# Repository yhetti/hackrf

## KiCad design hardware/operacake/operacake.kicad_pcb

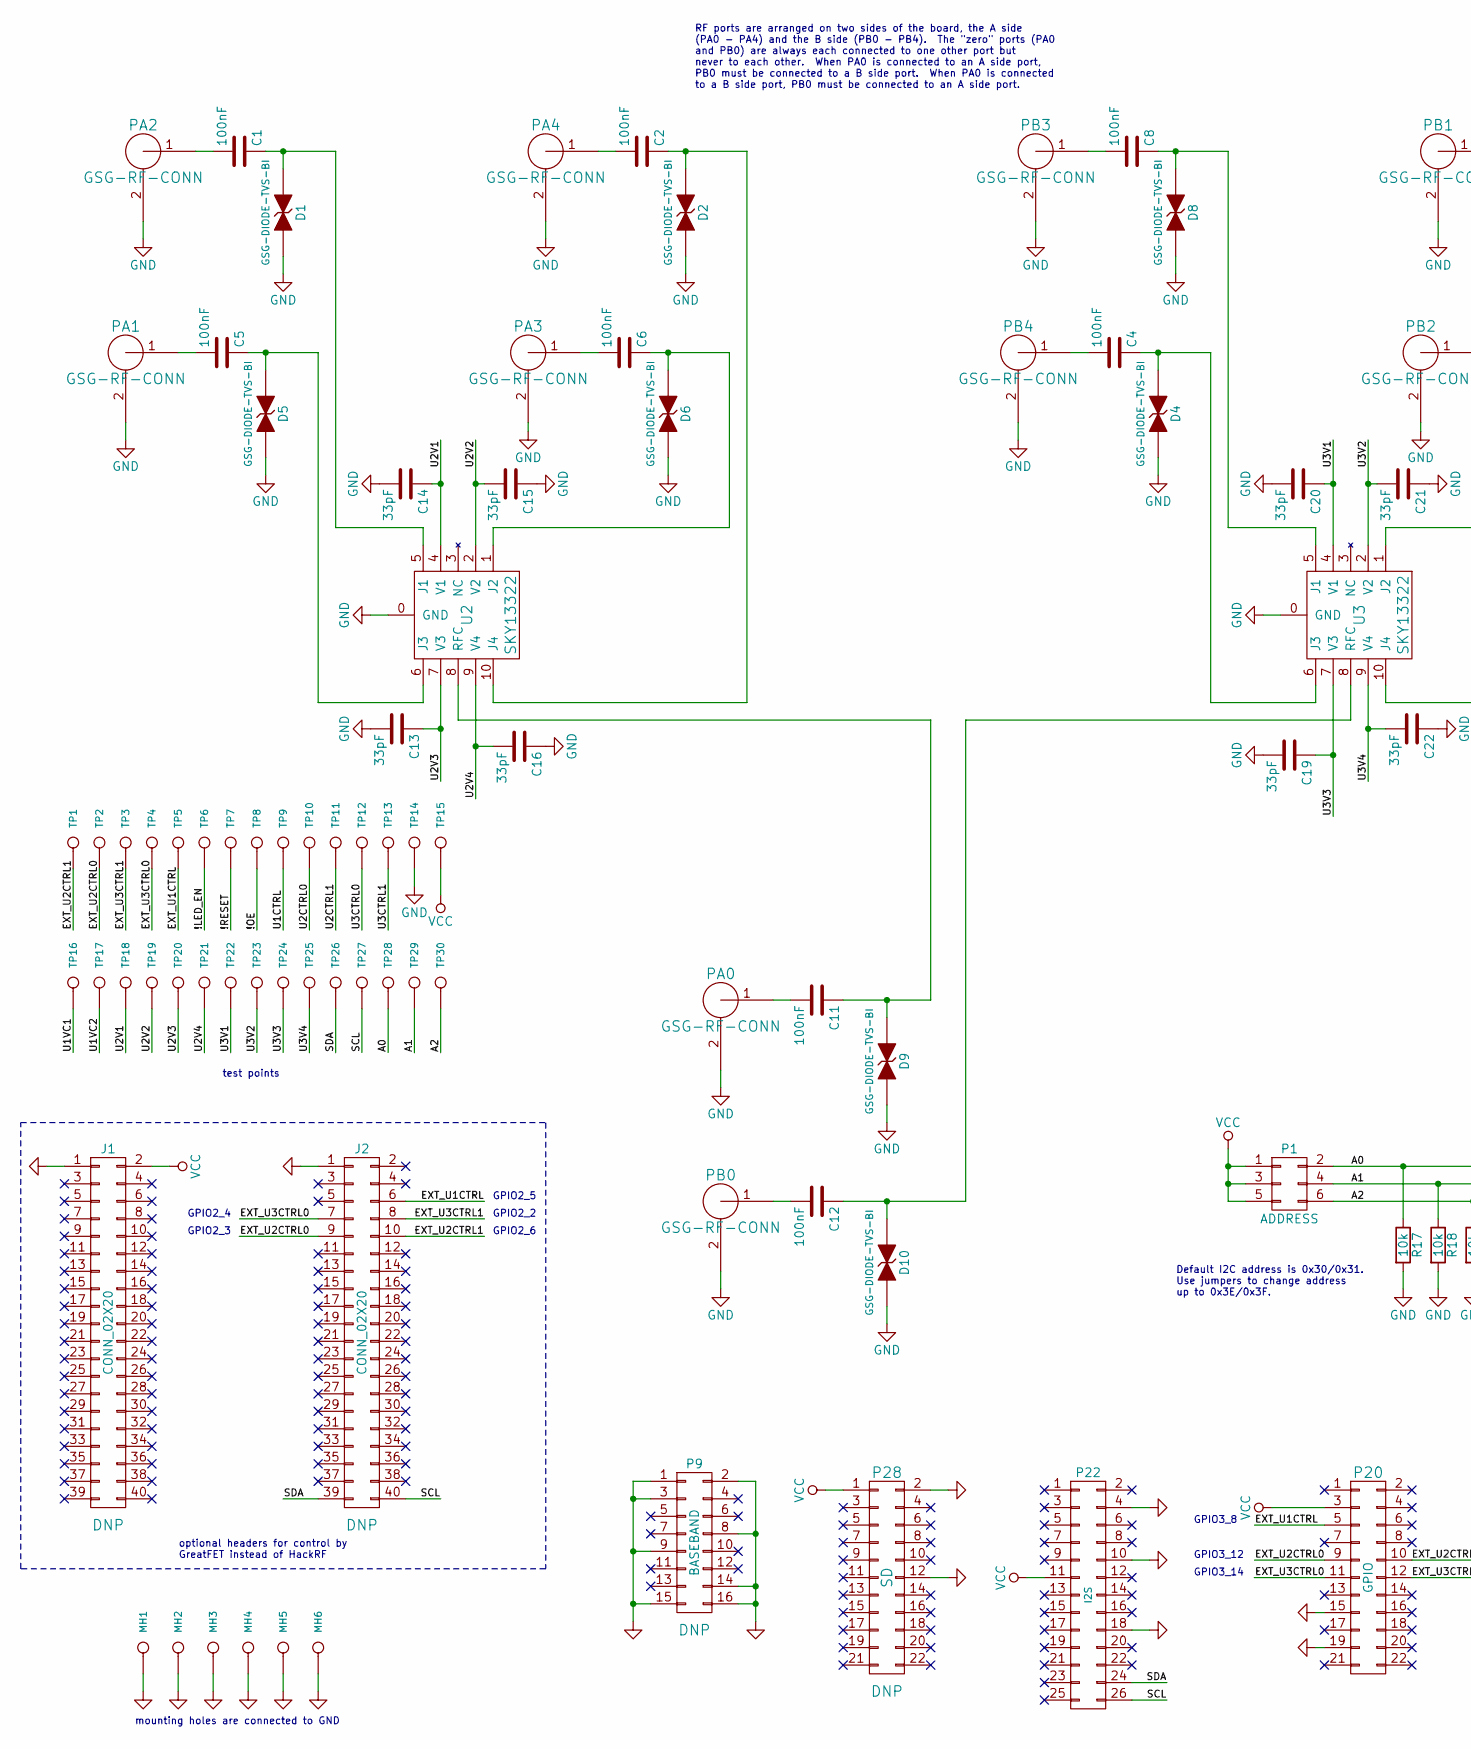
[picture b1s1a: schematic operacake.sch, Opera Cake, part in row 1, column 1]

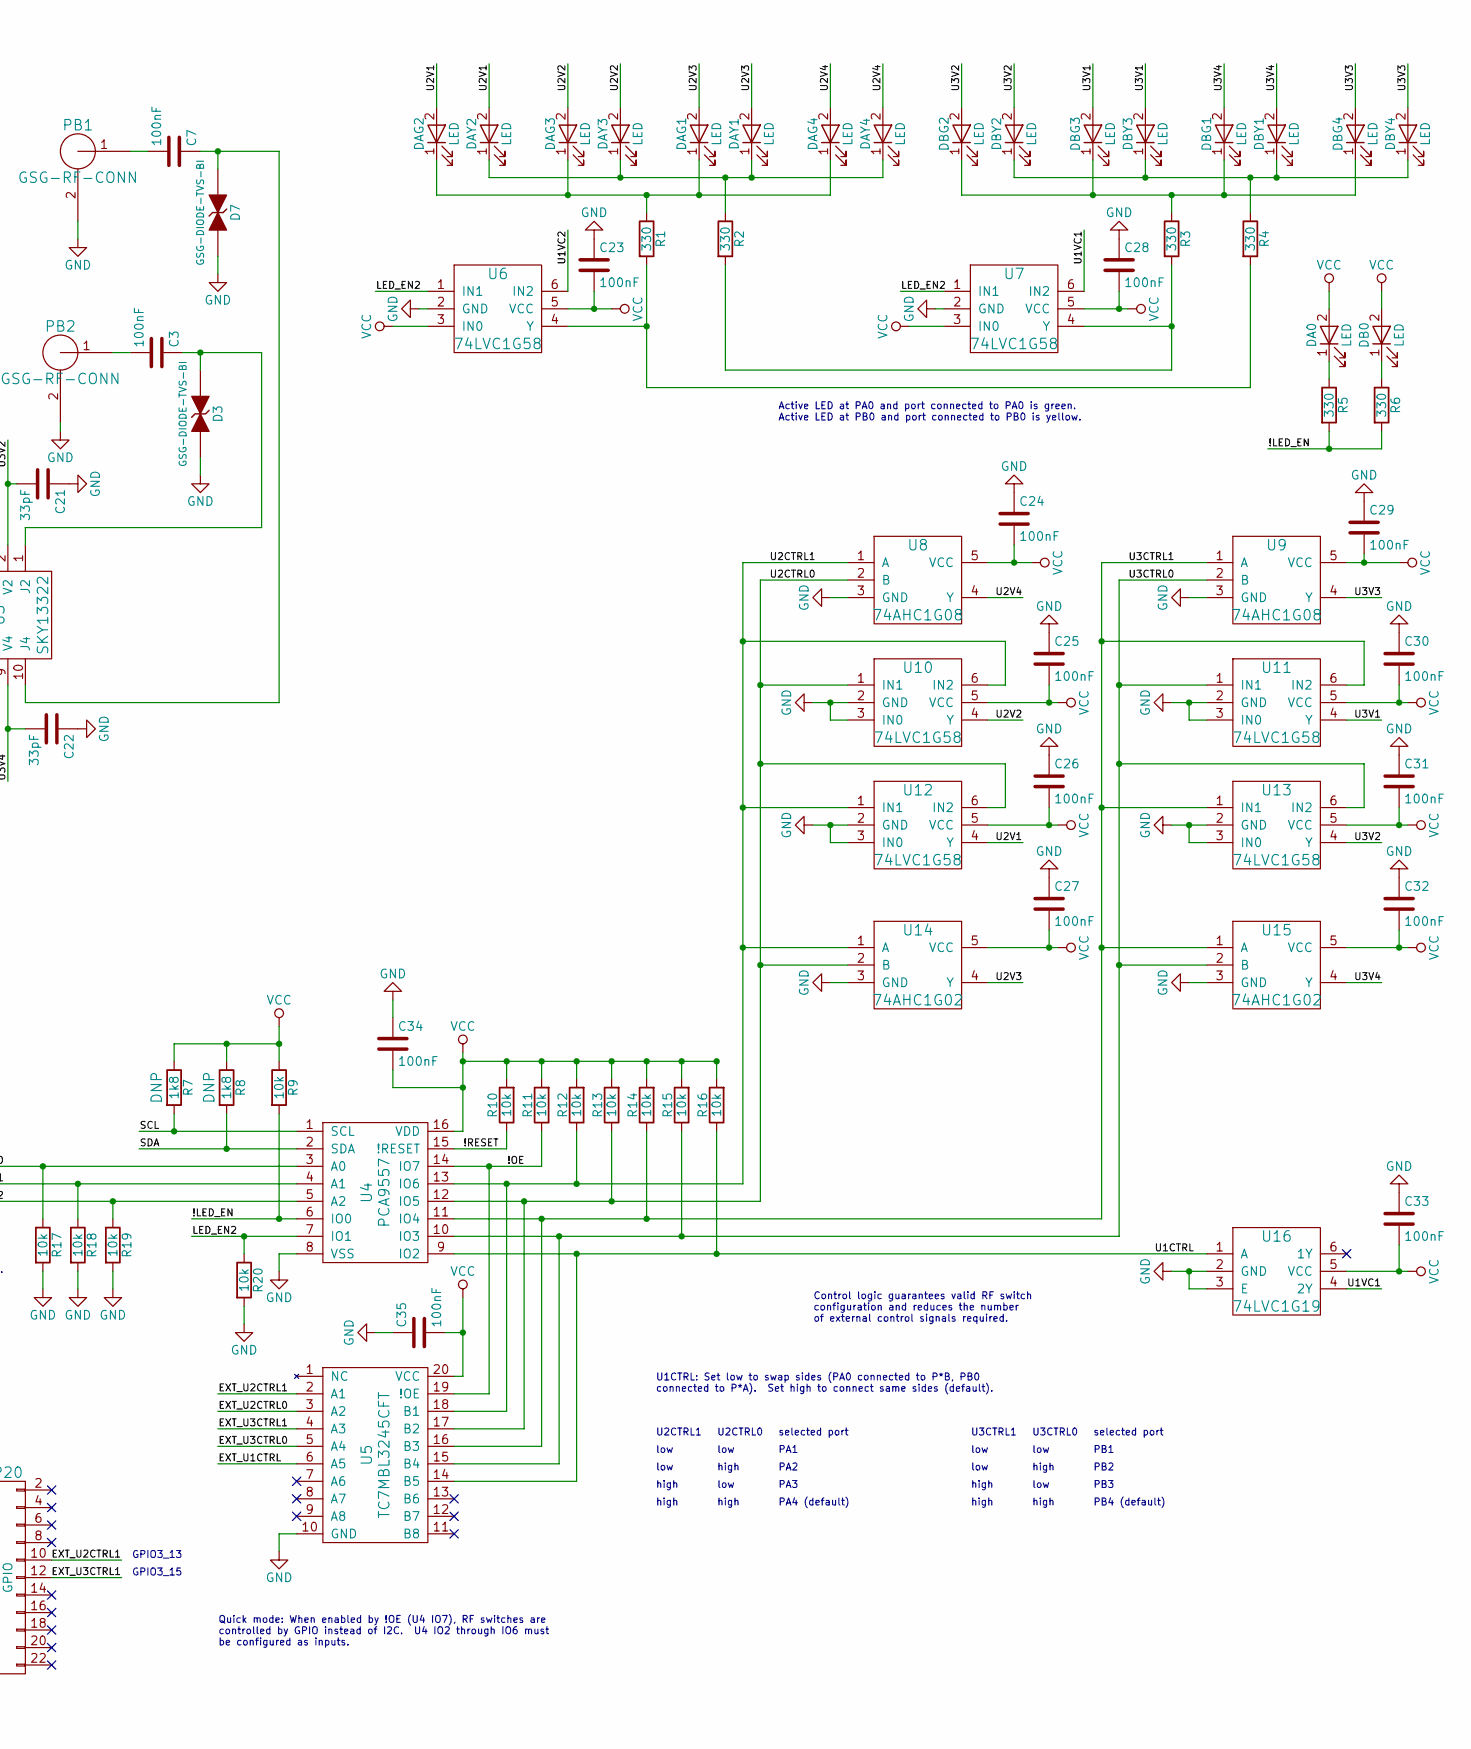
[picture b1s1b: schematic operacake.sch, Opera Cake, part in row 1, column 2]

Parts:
C1, C2, C3, C4, C5, C6, C7, C8, C11, C12, C23, C24, C25, C26, C27, C28, C29, C30, C31, C32, C33, C34, C35: 100nF; 0402; Part Number GRM155R61A104KA01D
C13, C14, C15, C16, C19, C20, C21, C22: 33pF; 0402; Part Number GRM1555C1H330JA01D
D1, D2, D3, D4, D5, D6, D7, D8, D9, D10: GSG-DIODE-TVS-BI; 0402; Part Number LXES15AAA1-153
DA0: LED; 0603D; Part Number SML-LX0603GW-TR
DAG1, DAG2, DAG3, DAG4: LED; 0603D; Part Number SML-LX0603GW-TR
DAY1, DAY2, DAY3, DAY4: LED; 0603D; Part Number SML-LX0603YW-TR
DB0: LED; 0603D; Part Number SML-LX0603YW-TR
DBG1, DBG2, DBG3, DBG4: LED; 0603D; Part Number SML-LX0603GW-TR
DBY1, DBY2, DBY3, DBY4: LED; 0603D; Part Number SML-LX0603YW-TR
J1, J2: CONN_02X20; HEADER-2x20-REVERSE
MH1, MH2, MH3, MH4, MH5, MH6: MOUNTING_HOLE; HOLE126MIL-COPPER
P1: ADDRESS; HEADER-2x3
P9: BASEBAND; HEADER-2x8
P20: GPIO; HEADER-2x11
P22: I2S; HEADER-2x13
P28: SD; HEADER-2x11
PA0, PA1, PA2, PA3, PA4: GSG-RF-CONN; GSG-SMA-73251-2120; Part Number 73251-2121
PB0, PB1, PB2, PB3, PB4: GSG-RF-CONN; GSG-SMA-73251-2120; Part Number 73251-2121
R1, R2, R3, R4, R5, R6: 330; 0603; Part Number RMCF0603JT330R
R7, R8: 1k8; 0603
R9, R10, R11, R12, R13, R14, R15, R16, R17, R18, R19, R20: 10k; 0603; Part Number ERJ-3GEYJ103V
TP1, TP2, TP3, TP4, TP5, TP6, TP7, TP8, TP9, TP10, TP11, TP12, TP13, TP14, TP15, TP16, TP17, TP18, TP19, TP20, TP21, TP22, TP23, TP24, TP25, TP26, TP27, TP28, TP29, TP30: CONN_1; TESTPOINT-50MIL
U2, U3: SKY13322; SKY13322-375LF; Part Number SKY13322-375LF
U4: PCA9557; TSSOP16; Part Number PCA9557PW,118
U5: TC7MBL3245CFT; TSSOP20; Part Number TC7MBL3245CFT(EL)
U6, U7, U10, U11, U12, U13: 74LVC1G58; SOT363; Part Number 74LVC1G58DW-7
U8, U9: 74AHC1G08; SOT353-1; Part Number 74AHC1G08SE-7
U14, U15: 74AHC1G02; SOT353-1; Part Number 74AHC1G02SE-7
U16: 74LVC1G19; SOT363; Part Number 74LVC1G19GW,125

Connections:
/!LED_EN: R5.2, R6.2, R9.2, TP6.1, U4.6 (IO0)
/!OE: R11.1, TP8.1, U4.14 (IO7), U5.19 (!OE)
/!RESET: R10.1, TP7.1, U4.15 (!RESET)
/A0: P1.2, R17.1, TP28.1, U4.3 (A0)
/A1: P1.4, R18.1, TP29.1, U4.4 (A1)
/A2: P1.6, R19.1, TP30.1, U4.5 (A2)
/EXT_U1CTRL: J2.6, P20.5, TP5.1, U5.6 (A5)
/EXT_U2CTRL0: J2.9, P20.9, TP2.1, U5.3 (A2)
/EXT_U2CTRL1: J2.10, P20.10, TP1.1, U5.2 (A1)
/EXT_U3CTRL0: J2.7, P20.11, TP4.1, U5.5 (A4)
/EXT_U3CTRL1: J2.8, P20.12, TP3.1, U5.4 (A3)
/LED_EN2: R20.1, U4.7 (IO1), U6.1 (IN1), U7.1 (IN1)
/SCL: J2.40, P22.26, R7.2, TP27.1, U4.1 (SCL)
/SDA: J2.39, P22.24, R8.2, TP26.1, U4.2 (SDA)
/U1CTRL: R16.1, TP9.1, U4.9 (IO2), U5.14 (B5), U16.1 (A)
/U1VC1: TP16.1, U7.6 (IN2), U16.4 (2Y)
/U1VC2: TP17.1, U6.6 (IN2)
/U2CTRL0: R13.1, TP10.1, U4.12 (IO5), U5.17 (B2), U8.2 (B), U10.1 (IN1), U12.6 (IN2), U14.2 (B)
/U2CTRL1: R12.1, TP11.1, U4.13 (IO6), U5.18 (B1), U8.1 (A), U10.6 (IN2), U12.1 (IN1), U14.1 (A)
/U2V1: C14.1, DAG2.2 (A), DAY2.2 (A), TP18.1, U2.4 (V1), U12.4 (Y)
/U2V2: C15.2, DAG3.2 (A), DAY3.2 (A), TP19.1, U2.2 (V2), U10.4 (Y)
/U2V3: C13.1, DAG1.2 (A), DAY1.2 (A), TP20.1, U2.7 (V3), U14.4 (Y)
/U2V4: C16.2, DAG4.2 (A), DAY4.2 (A), TP21.1, U2.9 (V4), U8.4 (Y)
/U3CTRL0: R15.1, TP12.1, U4.10 (IO3), U5.15 (B4), U9.2 (B), U11.1 (IN1), U13.6 (IN2), U15.2 (B)
/U3CTRL1: R14.1, TP13.1, U4.11 (IO4), U5.16 (B3), U9.1 (A), U11.6 (IN2), U13.1 (IN1), U15.1 (A)
/U3V1: C20.1, DBG3.2 (A), DBY3.2 (A), TP22.1, U3.4 (V1), U11.4 (Y)
/U3V2: C21.2, DBG2.2 (A), DBY2.2 (A), TP23.1, U3.2 (V2), U13.4 (Y)
/U3V3: C19.1, DBG4.2 (A), DBY4.2 (A), TP24.1, U3.7 (V3), U9.4 (Y)
/U3V4: C22.2, DBG1.2 (A), DBY1.2 (A), TP25.1, U3.9 (V4), U15.4 (Y)
GND: C13.2, C14.2, C15.1, C16.1, C19.2, C20.2, C21.1, C22.1, C23.1, C24.1, C25.1, C26.1, C27.1, C28.1, C29.1, C30.1, C31.1, C32.1, C33.1, C34.1, C35.1, D1.2 (K), D2.2 (K), D3.2 (K), D4.2 (K), D5.2 (K), D6.2 (K), D7.2 (K), D8.2 (K), D9.2 (K), D10.2 (K), J1.1, J2.1, MH1.1, MH2.1, MH3.1, MH4.1, MH5.1, MH6.1, P9.1, P9.2, P9.3, P9.8, P9.9, P9.14, P9.15, P9.16, P20.15, P20.19, P22.4, P22.10, P22.18, P28.2, P28.12, PA0.2 (GND), PA1.2 (GND), PA2.2 (GND), PA3.2 (GND), PA4.2 (GND), PB0.2 (GND), PB1.2 (GND), PB2.2 (GND), PB3.2 (GND), PB4.2 (GND), R17.2, R18.2, R19.2, R20.2, TP14.1, U2.0 (GND), U3.0 (GND), U4.8 (VSS), U5.10 (GND), U6.2 (GND), U7.2 (GND), U8.3 (GND), U9.3 (GND), U10.2 (GND), U10.3 (IN0), U11.2 (GND), U11.3 (IN0), U12.2 (GND), U12.3 (IN0), U13.2 (GND), U13.3 (IN0), U14.3 (GND), U15.3 (GND), U16.2 (GND), U16.3 (E)
unnamed: C1.1, D1.1 (A), U2.5 (J1)
unnamed: C1.2, PA2.1 (RF)
unnamed: C2.1, D2.1 (A), U2.10 (J4)
unnamed: C2.2, PA4.1 (RF)
unnamed: C3.1, D3.1 (A), U3.1 (J2)
unnamed: C3.2, PB2.1 (RF)
unnamed: C4.1, D4.1 (A), U3.6 (J3)
unnamed: C4.2, PB4.1 (RF)
unnamed: C5.1, D5.1 (A), U2.6 (J3)
unnamed: C5.2, PA1.1 (RF)
unnamed: C6.1, D6.1 (A), U2.1 (J2)
unnamed: C6.2, PA3.1 (RF)
unnamed: C7.1, D7.1 (A), U3.10 (J4)
unnamed: C7.2, PB1.1 (RF)
unnamed: C8.1, D8.1 (A), U3.5 (J1)
unnamed: C8.2, PB3.1 (RF)
unnamed: C11.1, D9.1 (A), U2.8 (RFC)
unnamed: C11.2, PA0.1 (RF)
unnamed: C12.1, D10.1 (A), U3.8 (RFC)
unnamed: C12.2, PB0.1 (RF)
unnamed: DA0.1 (K), R5.1
unnamed: DAG1.1 (K), DAG2.1 (K), DAG3.1 (K), DAG4.1 (K), R1.1
unnamed: DAY1.1 (K), DAY2.1 (K), DAY3.1 (K), DAY4.1 (K), R2.1
unnamed: DB0.1 (K), R6.1
unnamed: DBG1.1 (K), DBG2.1 (K), DBG3.1 (K), DBG4.1 (K), R3.1
unnamed: DBY1.1 (K), DBY2.1 (K), DBY3.1 (K), DBY4.1 (K), R4.1
unnamed: R1.2, R4.2, U6.4 (Y)
unnamed: R2.2, R3.2, U7.4 (Y)
VCC: C23.2, C24.2, C25.2, C26.2, C27.2, C28.2, C29.2, C30.2, C31.2, C32.2, C33.2, C34.2, C35.2, DA0.2 (A), DB0.2 (A), J1.2, P1.1, P1.3, P1.5, P20.3, P22.11, P28.1, R7.1, R8.1, R9.1, R10.2, R11.2, R12.2, R13.2, R14.2, R15.2, R16.2, TP15.1, U4.16 (VDD), U5.20 (VCC), U6.3 (IN0), U6.5 (VCC), U7.3 (IN0), U7.5 (VCC), U8.5 (VCC), U9.5 (VCC), U10.5 (VCC), U11.5 (VCC), U12.5 (VCC), U13.5 (VCC), U14.5 (VCC), U15.5 (VCC), U16.5 (VCC)

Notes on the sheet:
mounting holes are connected to GND
test points
Quick mode: When enabled by !OE (U4 IO7), RF switches are controlled by GPIO instead of I2C. U4 IO2 through IO6 must be configured as inputs.
Control logic guarantees valid RF switch configuration and reduces the number of external control signals required.
Active LED at PA0 and port connected to PA0 is green. Active LED at PB0 and port connected to PB0 is yellow.
Default I2C address is 0x30/0x31. Use jumpers to change address up to 0x3E/0x3F.
optional headers for control by GreatFET instead of HackRF
GPIO3_13
GPIO3_15
GPIO3_12
GPIO3_14
GPIO3_8
GPIO2_5
GPIO2_4
GPIO2_2
GPIO2_6
GPIO2_3
RF ports are arranged on two sides of the board, the A side (PA0 - PA4) and the B side (PB0 - PB4). The "zero" ports (PA0 and PB0) are always each connected to one other port but never to each other. When PA0 is connected to an A side port, PB0 must be connected to a B side port. When PA0 is connec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
U1CTRL: Set low to swap sides (PA0 connected to P*B, PB0 connected to P*A). Set high to connect same sides (default).
U2CTRL1
U2CTRL0
selected port
low
high
PA1
PA2
PA3
PA4 (default)
U3CTRL1
U3CTRL0
PB1
PB2
PB3
PB4 (default)

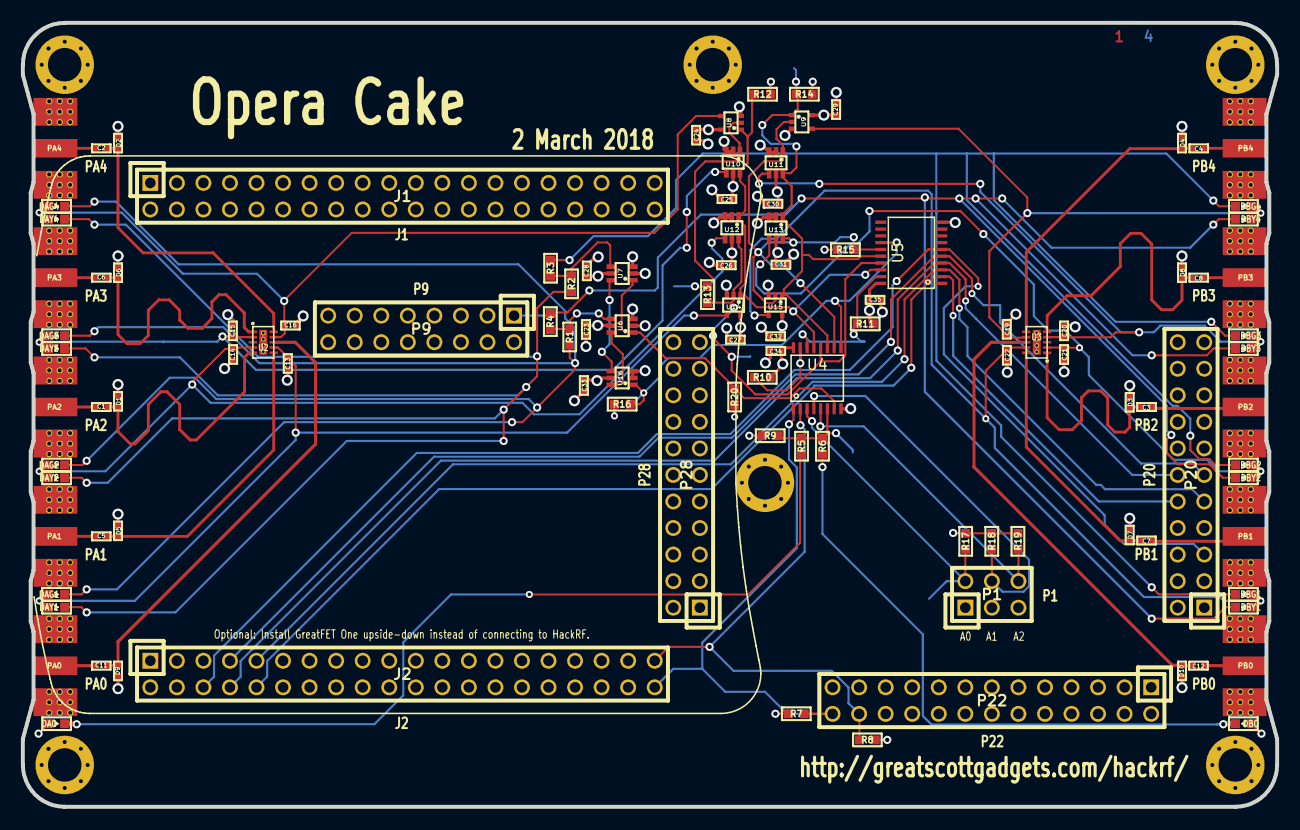
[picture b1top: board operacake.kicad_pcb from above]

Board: 4 copper layers, 120.0 x 75.0 mm, 145 parts (0 on the bottom side), 58 nets.

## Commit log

2018-02-28 Changed schematic and PCB to a design that seperates the PA & PB sides. No crossover will be possible with this design.
2018-03-03 Changed date on silkscreen.

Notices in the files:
hardware/operacake/operacake.sch:
Copyright 2016 Great Scott Gadgets
License: GPL v2
